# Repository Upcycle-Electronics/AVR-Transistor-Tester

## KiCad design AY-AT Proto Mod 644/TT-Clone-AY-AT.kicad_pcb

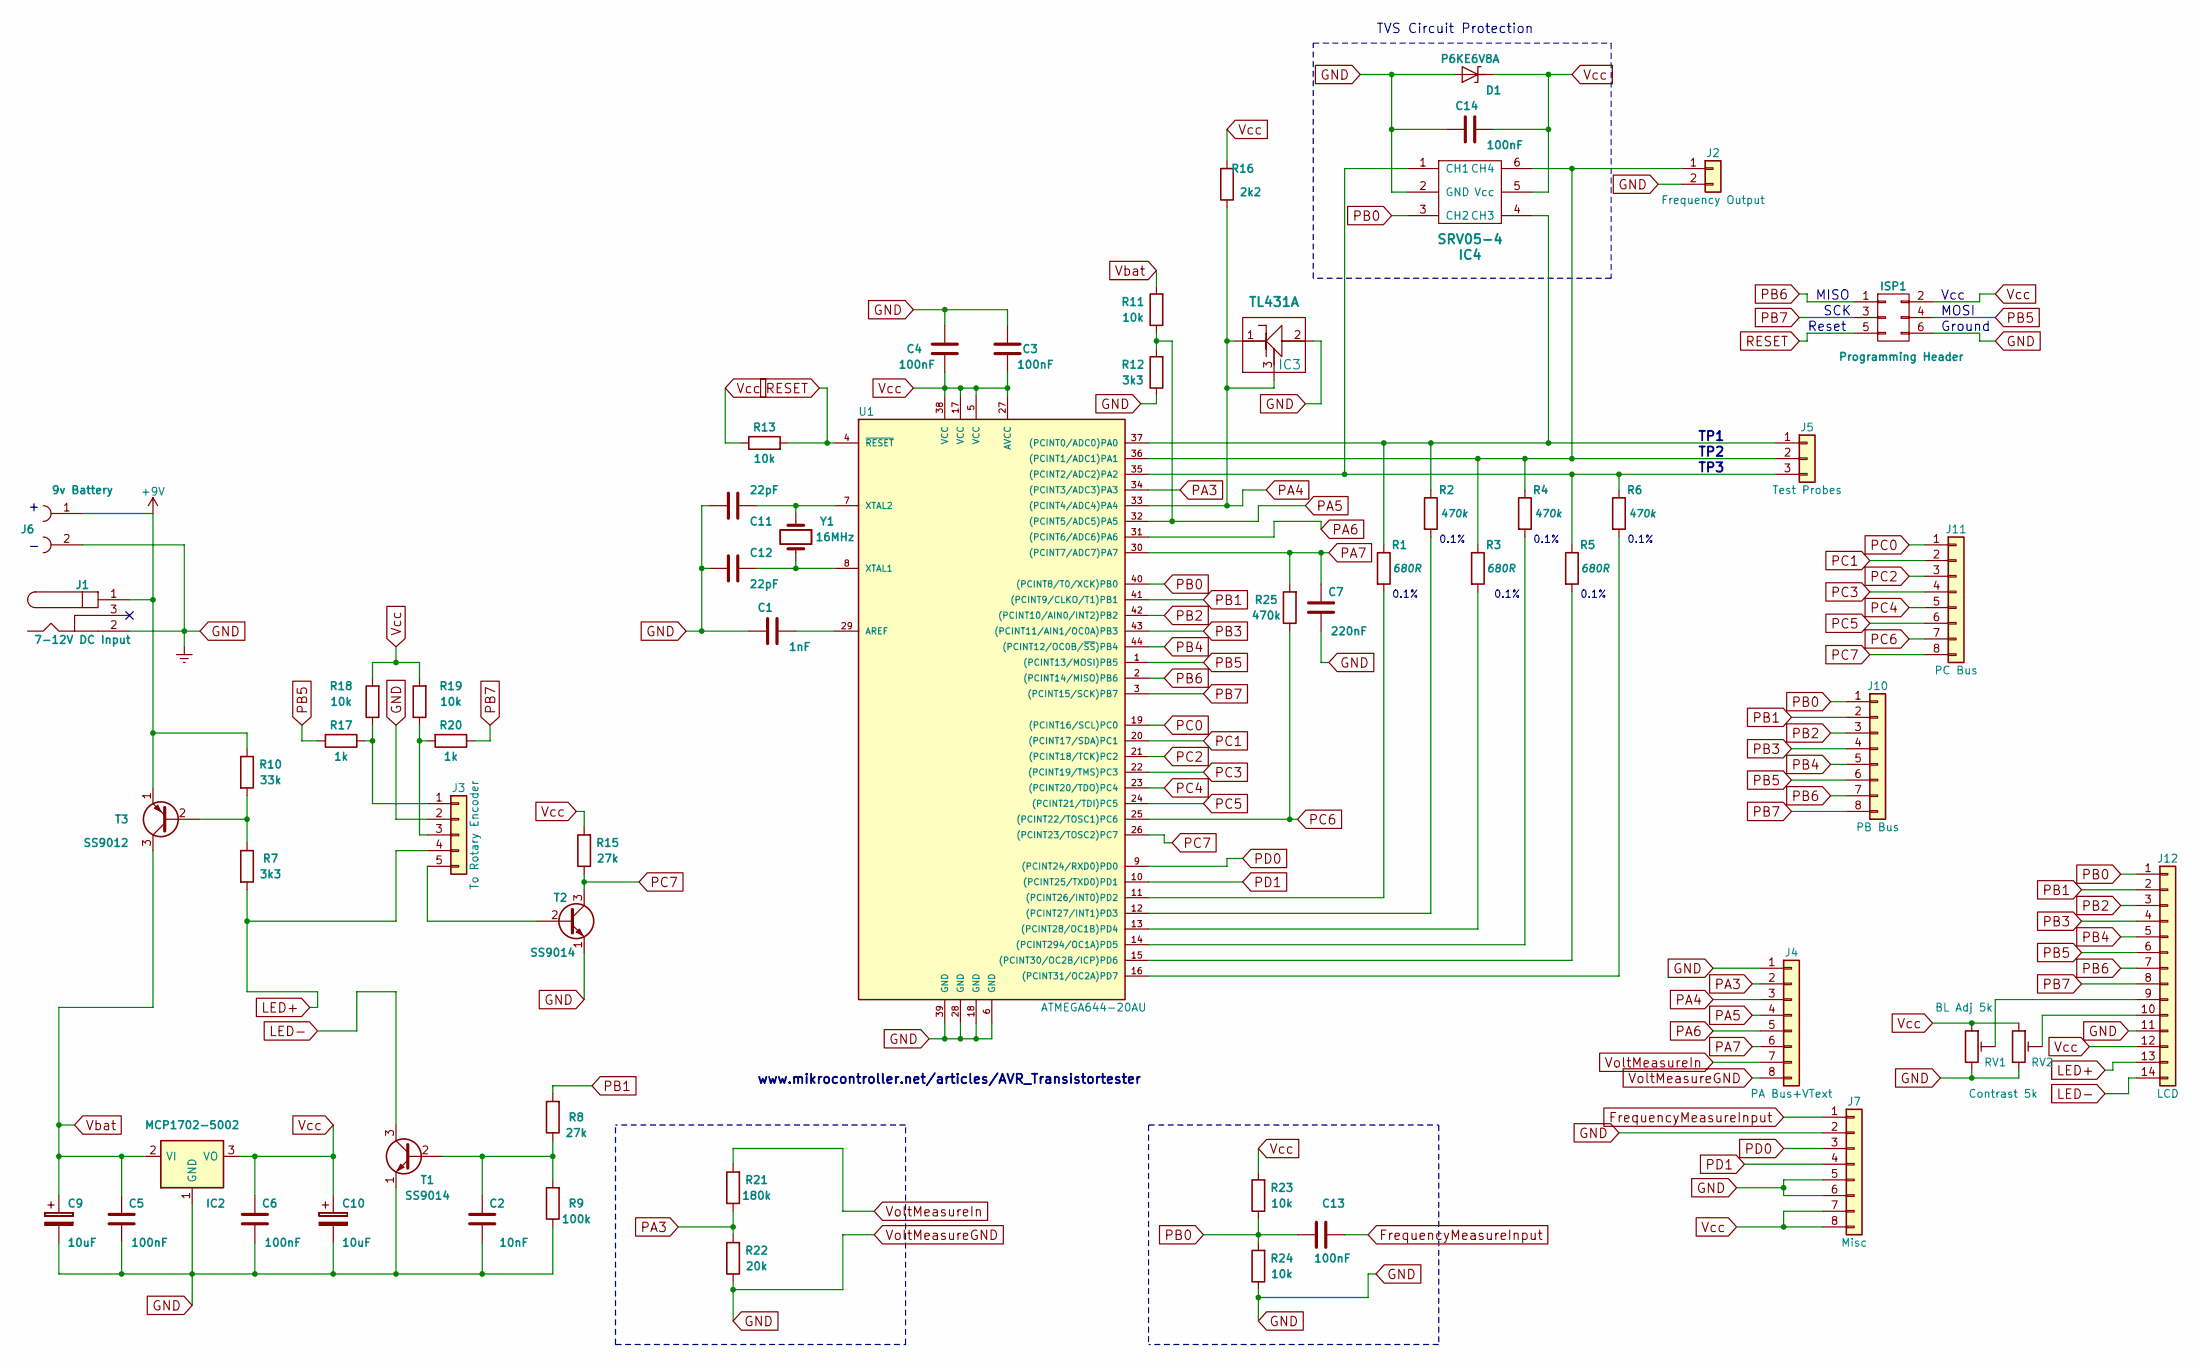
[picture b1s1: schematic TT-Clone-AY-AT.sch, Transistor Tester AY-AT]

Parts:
C1: 1nF; C_0805_HandSoldering
C2: 10nF; C_0805_HandSoldering
C3, C4, C5, C6, C13, C14: 100nF; C_0805_HandSoldering
C7: 220nF; C_0805_HandSoldering
C9, C10: 10uF; CP_Radial_D6.3mm_P2.50mm
C11, C12: 22pF; C_0805_HandSoldering
D1: P6KE6V8A; D_SMA
IC2: MCP1702-5002; TO-92_Inline_Narrow_Oval
IC3: TL431A; TO-92_Molded_Narrow
IC4: SRV05-4; SOT-23-6
ISP1: Programming Header; Pin_Header_Angled_2x03_Pitch2.54mm
J1: 7-12V DC Input; BARREL_JACK
J2: Frequency Output; Socket_Strip_Straight_1x02_Pitch2.54mm
J3: To Rotary Encoder; Socket_Strip_Straight_1x05_Pitch2.54mm
J4: PA Bus+VText; Socket_Strip_Straight_1x08_Pitch2.54mm
J5: Test Probes; Socket_Strip_Straight_1x03_Pitch2.54mm
J6: 9v Battery; PINHEAD1-2
J7: Misc; Socket_Strip_Straight_1x08_Pitch2.54mm
J10: PB Bus; Socket_Strip_Straight_1x08_Pitch2.54mm
J11: PC Bus; Socket_Strip_Straight_1x08_Pitch2.54mm
J12: LCD; Pin_Header_Straight_1x14_Pitch2.54mm
R1, R3, R5: 680R; R_Axial_DIN0207_L6.3mm_D2.5mm_P7.62mm_Horizontal
R2, R4, R6, R25: 470k; R_Axial_DIN0207_L6.3mm_D2.5mm_P7.62mm_Horizontal
R7, R12: 3k3; R_0805_HandSoldering
R8, R15: 27k; R_0805_HandSoldering
R9: 100k; R_0805_HandSoldering
R10: 33k; R_0805_HandSoldering
R11, R13, R18, R19, R23, R24: 10k; R_0805_HandSoldering
R16: 2k2; R_0805_HandSoldering
R17, R20: 1k; R_0805_HandSoldering
R21: 180k; R_0805_HandSoldering
R22: 20k; R_0805_HandSoldering
RV1: BL Adj 5k; Potentiometer_Trimmer_Bourns_3296W
RV2: Contrast 5k; Potentiometer_Trimmer_Bourns_3296W
T1, T2: SS9014; TO-92_Inline_Narrow_Oval
T3: SS9012; TO-92_Inline_Narrow_Oval
U1: ATMEGA644-20AU; TQFP-44_10x10mm_Pitch0.8mm
Y1: 16MHz; Crystal_HC49-4H_Vertical

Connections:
+9V: J1.1, J6.1, R10.1, T3.1 (E)
FrequencyMeasureInput: C13.1, J7.1
LED+: J3.4, J12.13, R7.2
LED-: J12.14, T1.3 (C)
unnamed: C1.1, U1.29 (AREF)
unnamed: C2.2, R8.1, R9.2, T1.2 (B)
unnamed: C11.1, U1.7 (XTAL2), Y1.1
unnamed: C12.1, U1.8 (XTAL1), Y1.2
unnamed: IC4.1 (CH1), J5.3, R5.1, R6.1, U1.35 ((PCINT2/ADC2)PA2)
unnamed: IC4.4 (CH3), J5.1, R1.1, R2.1, U1.37 ((PCINT0/ADC0)PA0)
unnamed: J3.1, R17.1, R18.1
unnamed: J3.3, R19.1, R20.2
unnamed: J3.5, T2.2 (B)
unnamed: J12.9, RV1.2
unnamed: J12.10, RV2.2
unnamed: R1.2, U1.11 ((PCINT26/INT0)PD2)
unnamed: R2.2, U1.12 ((PCINT27/INT1)PD3)
unnamed: R3.2, U1.13 ((PCINT28/OC1B)PD4)
unnamed: R4.2, U1.14 ((PCINT294/OC1A)PD5)
unnamed: R5.2, U1.15 ((PCINT30/OC2B/ICP)PD6)
unnamed: R6.2, U1.16 ((PCINT31/OC2A)PD7)
unnamed: R7.1, R10.2, T3.2 (B)
PA3: J4.2, R21.1, R22.2, U1.34 ((PCINT3/ADC3)PA3)
PA4: IC3.1, IC3.3, J4.3, R16.1, U1.33 ((PCINT4/ADC4)PA4)
PA5: J4.4, R11.1, R12.2, U1.32 ((PCINT5/ADC5)PA5)
PA6: J4.5, U1.31 ((PCINT6/ADC6)PA6)
PA7: C7.2, J4.6, R25.2, U1.30 ((PCINT7/ADC7)PA7)
PB0: C13.2, IC4.3 (CH2), J10.1, J12.1, R23.1, R24.2, U1.40 ((PCINT8/T0/XCK)PB0)
PB1: J10.2, J12.2, R8.2, U1.41 ((PCINT9/CLKO/T1)PB1)
PB2: J10.3, J12.3, U1.42 ((PCINT10/AIN0/INT2)PB2)
PB3: J10.4, J12.4, U1.43 ((PCINT11/AIN1/OC0A)PB3)
PB4: J10.5, J12.5, U1.44 ((PCINT12/OC0B/~SS~)PB4)
PB5: ISP1.4, J10.6, J12.6, R17.2, U1.1 ((PCINT13/MOSI)PB5)
PB6: ISP1.1, J10.7, J12.7, U1.2 ((PCINT14/MISO)PB6)
PB7: ISP1.3, J10.8, J12.8, R20.1, U1.3 ((PCINT15/SCK)PB7)
PC0: J11.1, U1.19 ((PCINT16/SCL)PC0)
PC1: J11.2, U1.20 ((PCINT17/SDA)PC1)
PC2: J11.3, U1.21 ((PCINT18/TCK)PC2)
PC3: J11.4, U1.22 ((PCINT19/TMS)PC3)
PC4: J11.5, U1.23 ((PCINT20/TDO)PC4)
PC5: J11.6, U1.24 ((PCINT21/TDI)PC5)
PC6: J11.7, R25.1, U1.25 ((PCINT22/TOSC1)PC6)
PC7: J11.8, R15.1, T2.3 (C), U1.26 ((PCINT23/TOSC2)PC7)
PD0: J7.3, U1.9 ((PCINT24/RXD0)PD0)
PD1: J7.4, U1.10 ((PCINT25/TXD0)PD1)
RESET: ISP1.5, R13.2, U1.4 (~RESET)
Vbat: C5.2, C9.1, IC2.2 (VI), R11.2, T3.3 (C)
Vcc: C3.1, C4.2, C6.2, C10.1, C14.1, D1.1 (A1), IC2.3 (VO), IC4.5 (Vcc), ISP1.2, J7.7, J7.8, J12.12, R13.1, R15.2, R16.2, R18.2, R19.2, R23.2, RV1.1, RV2.1, U1.5 (VCC), U1.17 (VCC), U1.27 (AVCC), U1.38 (VCC)
VoltMeasureIn: J4.7, R21.2

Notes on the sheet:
MISO
SCK
MOSI
Reset
Vcc
Ground
0.1%
TVS Circuit Protection
www.mikrocontroller.net/articles/AVR_Transistortester
TP1
TP2
TP3

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
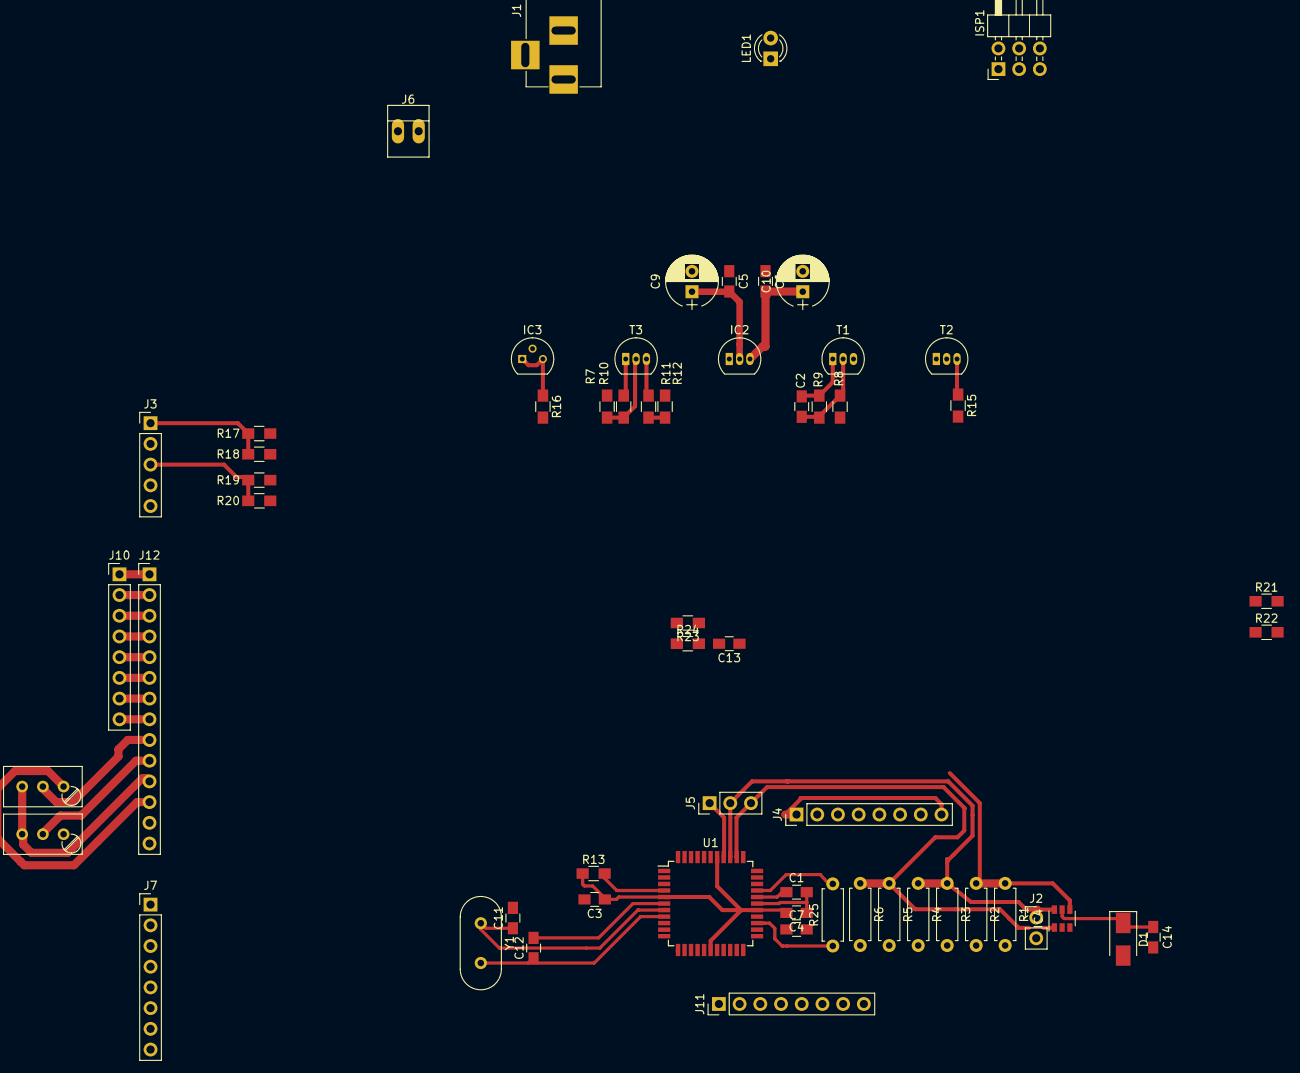
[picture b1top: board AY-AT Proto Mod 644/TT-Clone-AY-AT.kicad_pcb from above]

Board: 2 copper layers, 60 parts (0 on the bottom side), 51 nets.

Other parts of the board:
LED1: LED1; LED_D3.0mm

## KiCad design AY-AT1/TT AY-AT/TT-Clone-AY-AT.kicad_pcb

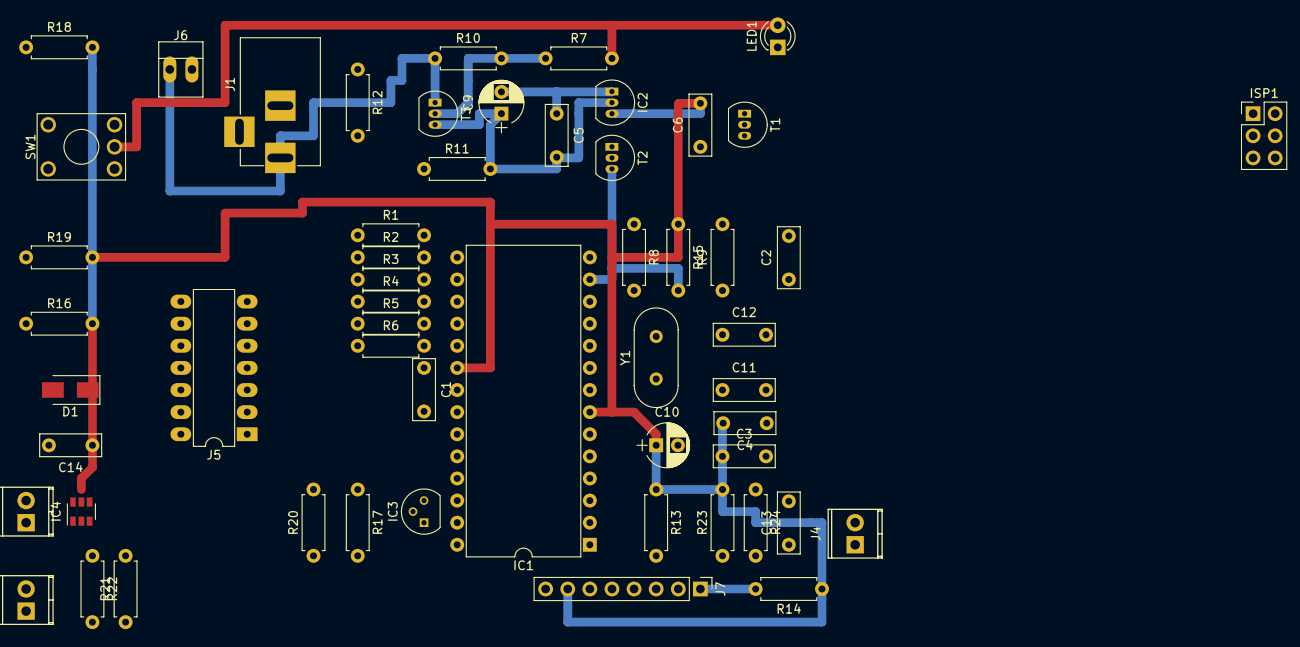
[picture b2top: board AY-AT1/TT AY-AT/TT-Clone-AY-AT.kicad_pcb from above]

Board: 2 copper layers, 55 parts (0 on the bottom side), 38 nets.

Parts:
C1: 1nF; C_Disc_D7.0mm_W2.5mm_P5.00mm
C2: 10nF; C_Disc_D7.0mm_W2.5mm_P5.00mm
C3, C4, C5, C6, C13, C14: 100nF; C_Disc_D7.0mm_W2.5mm_P5.00mm
C9, C10: 10uF; CP_Radial_D5.0mm_P2.50mm
C11, C12: 22pF; C_Disc_D7.0mm_W2.5mm_P5.00mm
D1: P6KE6V8A; D_SMA
IC1: ATmega328; DIP-28_W15.24mm
IC2: HT7550; TO-92_Inline_Narrow_Oval
IC3: TL431A; TO-92_Molded_Narrow
IC4: SRV05-4; SOT-23-6
ISP1: Programming Header; Pin_Header_Straight_2x03_Pitch2.54mm
J1: 7-12V DC Input; BARREL_JACK
J2: Frequency Out; TerminalBlock_Pheonix_MPT-2.54mm_2pol
J3: Voltmeter 0.1-45V; TerminalBlock_Pheonix_MPT-2.54mm_2pol
J4: Frequency Measure; TerminalBlock_Pheonix_MPT-2.54mm_2pol
J5: TT ZIF; DIP-14_W7.62mm_LongPads
J6: 9v Battery; PINHEAD1-2
J7: TFT LCD ST7735; Pin_Header_Straight_1x08_Pitch2.54mm
LED1: LED1; LED_D3.0mm
R1, R3, R5: 680R; R_Axial_DIN0207_L6.3mm_D2.5mm_P7.62mm_Horizontal
R2, R4, R6: 470k; R_Axial_DIN0207_L6.3mm_D2.5mm_P7.62mm_Horizontal
R7, R12: 3k3; R_Axial_DIN0207_L6.3mm_D2.5mm_P7.62mm_Horizontal
R8, R15: 27k; R_Axial_DIN0207_L6.3mm_D2.5mm_P7.62mm_Horizontal
R9: 100k; R_Axial_DIN0207_L6.3mm_D2.5mm_P7.62mm_Horizontal
R10: 33k; R_Axial_DIN0207_L6.3mm_D2.5mm_P7.62mm_Horizontal
R11, R13, R18, R19, R23, R24: 10k; R_Axial_DIN0207_L6.3mm_D2.5mm_P7.62mm_Horizontal
R14: 220R; R_Axial_DIN0207_L6.3mm_D2.5mm_P7.62mm_Horizontal
R16: 2k2; R_Axial_DIN0207_L6.3mm_D2.5mm_P7.62mm_Horizontal
R17, R20: 1k; R_Axial_DIN0207_L6.3mm_D2.5mm_P7.62mm_Horizontal
R21: 180k; R_Axial_DIN0207_L6.3mm_D2.5mm_P7.62mm_Horizontal
R22: 20k; R_Axial_DIN0207_L6.3mm_D2.5mm_P7.62mm_Horizontal
SW1: RE1; KSA_Tactile_SPST
T1, T2: SS9014; TO-92_Inline_Narrow_Oval
T3: SS9012; TO-92_Inline_Narrow_Oval
Y1: 8MHz; Crystal_HC49-4H_Vertical

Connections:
GND: C1.2, C2.1, C3.2, C4.1, C5.1, C6.1, C9.2, C10.2, C11.2, C12.2, C14.2, D1.2, IC1.8, IC1.22, IC2.1, IC3.2, IC4.2, J1.2, J2.2, J3.2, J4.2, J6.2, J7.8, R9.1, R12.1, R22.1, R24.1, SW1.2, T1.1, T2.1
unnamed: C1.1, IC1.21
unnamed: C2.2, R8.1, R9.2, T1.2
unnamed: C11.1, IC1.9, Y1.1
unnamed: C12.1, IC1.10, Y1.2
unnamed: C13.1, J4.1
unnamed: IC1.1, R13.2
unnamed: IC1.2, J7.2
unnamed: IC1.4, J7.5
unnamed: IC1.11, J7.6
unnamed: IC1.12, R8.2
unnamed: IC1.13, R15.2, T2.3
unnamed: IC1.14, R1.2
unnamed: IC1.15, R2.2
unnamed: IC1.16, R3.2
unnamed: IC1.17, R4.2
unnamed: IC1.18, R5.2
unnamed: IC1.19, R6.2
unnamed: IC1.23, IC4.4, J5.1, R1.1, R2.1
unnamed: IC1.24, IC4.6, J2.1, J5.2, R3.1, R4.1
unnamed: IC1.25, IC4.3, J5.3, R5.1, R6.1
unnamed: IC1.27, IC3.1, IC3.3, R16.1
unnamed: IC1.28, R11.1, R12.2
unnamed: J1.1, J6.1, R10.1, T3.1
unnamed: J3.1, R21.2
unnamed: J7.1, R14.2
unnamed: LED1.1, T1.3
unnamed: LED1.2, R7.2, SW1.4
unnamed: R7.1, R10.2, T3.2
unnamed: R17.1, R18.1, SW1.1
unnamed: R19.1, R20.2, SW1.3
unnamed: SW1.5, T2.2
PC3: IC1.26, R21.1, R22.2
PD1: IC1.3, J7.3, R17.2
PD3: IC1.5, J7.4, R20.1
PD4: C13.2, IC1.6, R23.1, R24.2
Vbat: C5.2, C9.1, IC2.2, R11.2, T3.3
Vcc: C3.1, C4.2, C6.2, C10.1, C14.1, D1.1, IC1.7, IC1.20, IC2.3, IC4.5, J7.7, R13.1, R14.1, R15.1, R16.2, R18.2, R19.2, R23.2

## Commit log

2017-11-25 Create AVR Bitmap U8G2 ST7920
2018-05-19 Create AY-AT1
2018-05-19 Create AY-AT Proto Mod 644
2018-05-19 Create Littlet
2018-05-19 Create TT Master Draft
2018-05-19 Create TT Custom Parts Library
